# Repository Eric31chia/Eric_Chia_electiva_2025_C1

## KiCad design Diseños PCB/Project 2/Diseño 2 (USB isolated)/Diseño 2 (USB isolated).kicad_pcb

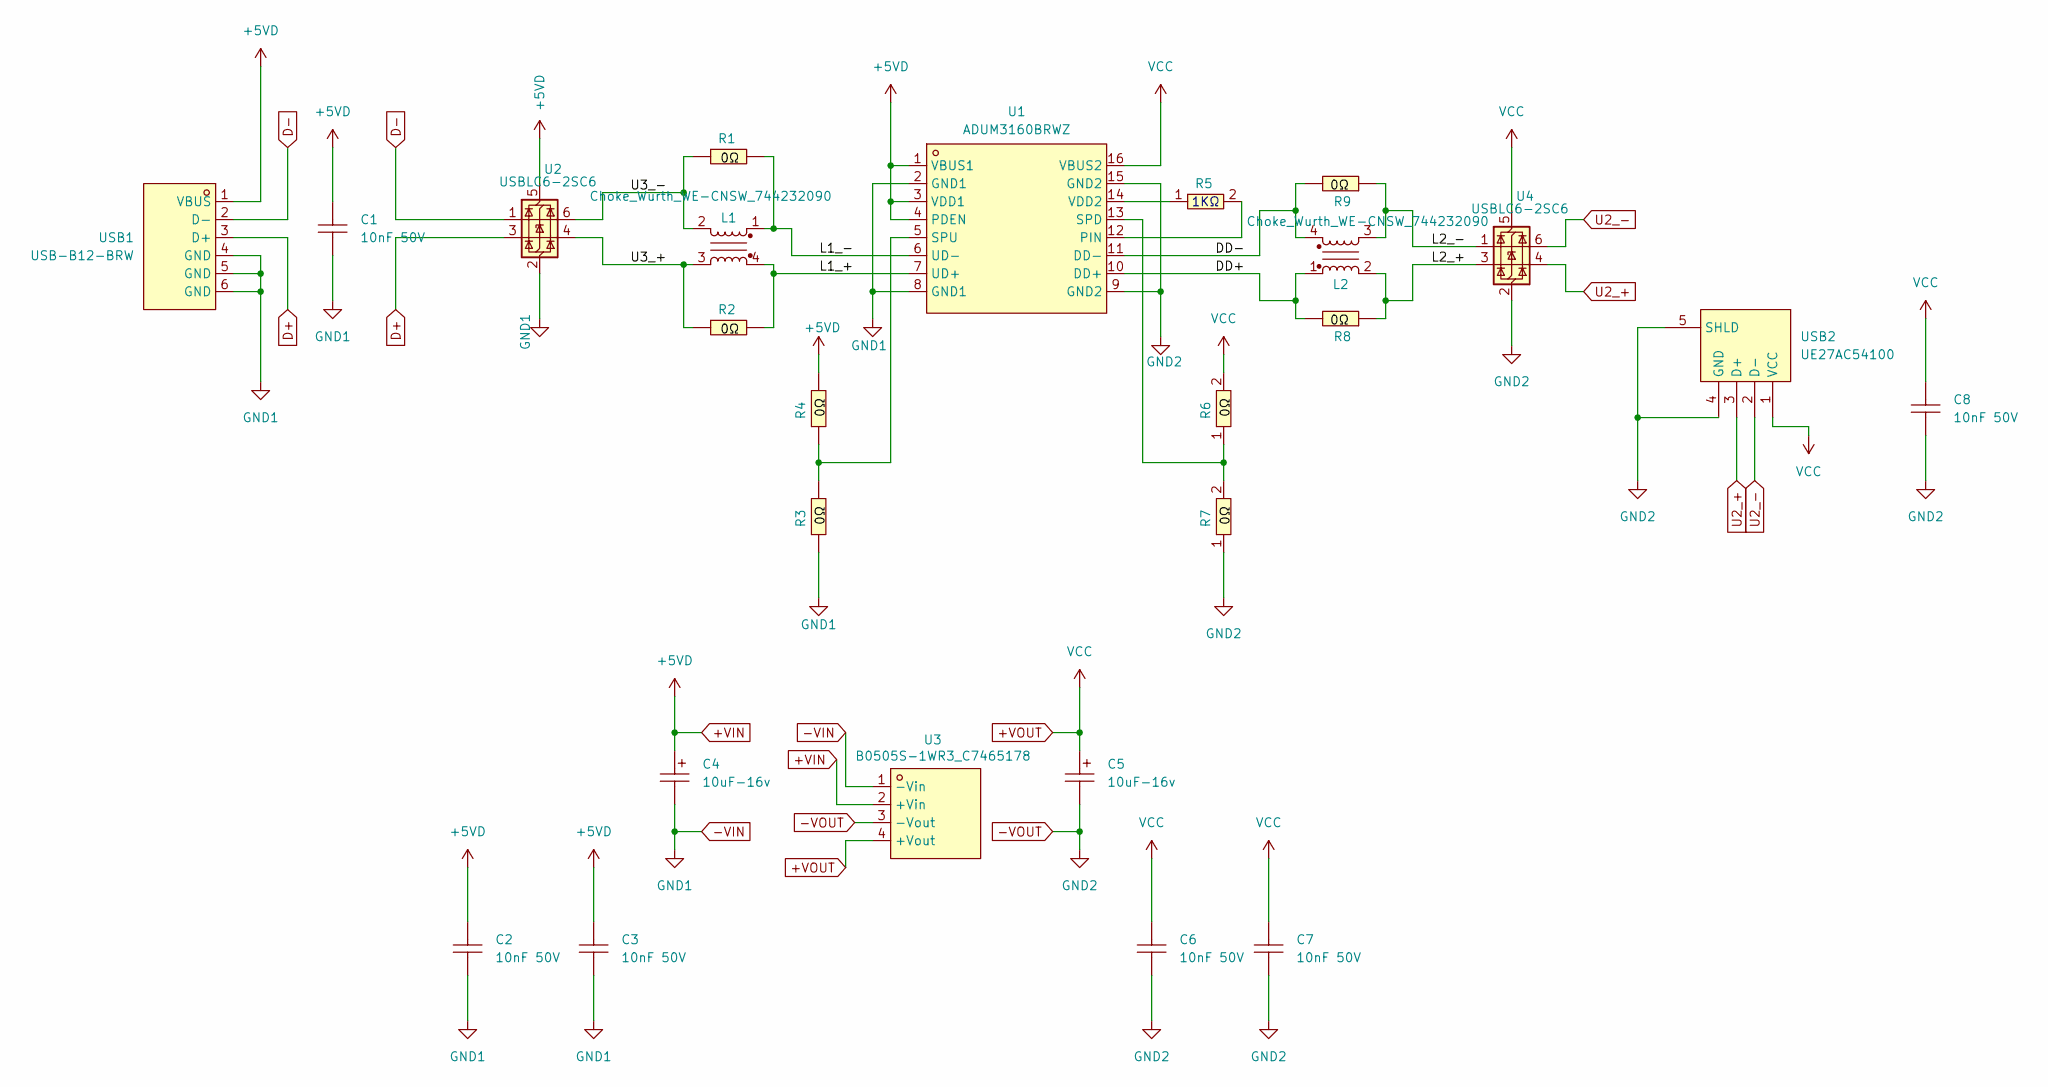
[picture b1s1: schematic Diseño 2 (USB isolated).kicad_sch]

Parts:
C1, C2, C3, C6, C7, C8: 10nF 50V; C0402; LCSC Part C60133
C4, C5: 10uF-16v; CAP-SMD_L3.2-W1.6-RD; LCSC Part C128254
L1, L2: Choke_Wurth_WE-CNSW_744232090; L_CommonMode_Wurth_WE-CNSW-1206
R1, R2, R3, R4, R5, R6, R7, R8, R9: RC0402FR-070RL; R0402; LCSC Part C106231
U1: ADUM3160BRWZ; WSOIC-16_L10.3-W7.5-P1.27-LS10.3-BL; LCSC Part C108501
U2, U4: USBLC6-2SC6; SOT-23-6
U3: B0505S-1WR3_C7465178; PWRM-TH_B0505S-1WR3; LCSC Part C7465178
USB1: USB-B12-BRW; USB-B-TH_USB-B12-BRW; LCSC Part C720550
USB2: UE27AC54100; USB-A-TH_UE27AC54100; LCSC Part C464564

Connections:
+VIN: C1.1, C2.1, C3.1, C4.1, R4.2, U1.1 (VBUS1), U1.3 (VDD1), U1.4 (PDEN), U2.5 (VBUS), U3.2 (+Vin), USB1.1 (VBUS)
+VOUT: C5.1, C6.1, C7.1, C8.1, R6.2, U1.16 (VBUS2), U3.4 (+Vout), U4.5 (VBUS), USB2.1 (VCC)
-VIN: C1.2, C2.2, C3.2, C4.2, R3.1, U1.2 (GND1), U1.8 (GND1), U2.2 (GND), U3.1 (-Vin), USB1.4 (GND), USB1.5 (GND), USB1.6 (GND)
-VOUT: C5.2, C6.2, C7.2, C8.2, R7.1, U1.9 (GND2), U1.15 (GND2), U3.3 (-Vout), U4.2 (GND), USB2.4 (GND), USB2.5 (SHLD)
/DD+: L2.1, R8.2, U1.10 (DD+)
/DD-: L2.4, R9.2, U1.11 (DD-)
/L1_+: L1.4, R2.2, U1.7 (UD+)
/L1_-: L1.1, R1.2, U1.6 (UD-)
/L2_+: L2.2, R8.1, U4.3 (I/O2)
/L2_-: L2.3, R9.1, U4.1 (I/O1)
/U3_+: L1.3, R2.1, U2.4 (I/O2)
/U3_-: L1.2, R1.1, U2.6 (I/O1)
D+: U2.3 (I/O2), USB1.3 (D+)
D-: U2.1 (I/O1), USB1.2 (D-)
unnamed: R5.2, U1.12 (PIN)
unnamed: R6.1, R7.2, U1.13 (SPD)
unnamed: R3.2, R4.1, U1.5 (SPU)
unnamed: R5.1, U1.14 (VDD2)
U2_+: U4.4 (I/O2), USB2.3 (D+)
U2_-: U4.6 (I/O1), USB2.2 (D-)

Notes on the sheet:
1KΩ

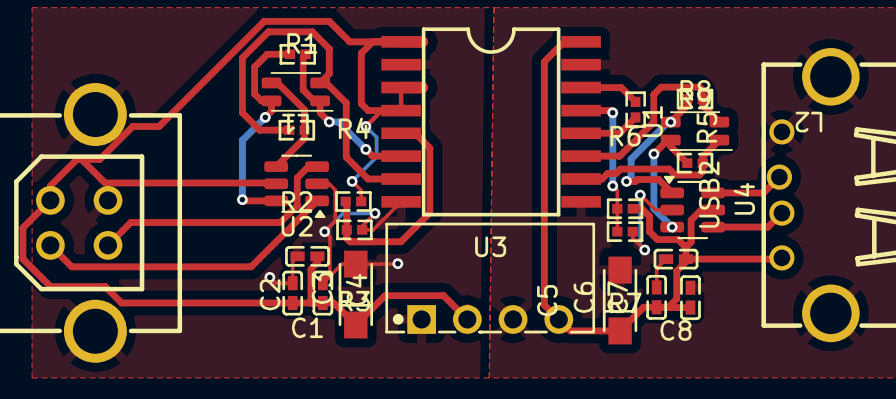
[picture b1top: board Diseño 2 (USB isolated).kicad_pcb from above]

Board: 2 copper layers, 25 parts (0 on the bottom side), 20 nets.

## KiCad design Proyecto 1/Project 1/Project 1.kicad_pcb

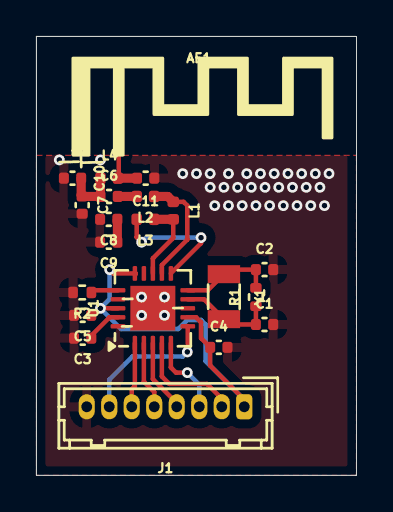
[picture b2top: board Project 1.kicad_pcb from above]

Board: 2 copper layers, 17.8 x 24.4 mm, 21 parts (0 on the bottom side), 18 nets.

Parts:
AE1: Antenna; Texas_SWRA117D_2.4GHz_Right
C1, C2: 22p; C_0402_1005Metric
C3, C4, C5: C_Small; C_0402_1005Metric
C6: 1p5; C_0402_1005Metric
C7: 1p; C_0402_1005Metric
C8: 10n; C_0402_1005Metric
C9: 1n; C_0402_1005Metric
C10, C11: Cx; C_0402_1005Metric
J1: Conn_01x08_Pin; Hirose_DF13-08P-1.25DSA_1x08_P1.25mm_Vertical
L1: 8n2; L_0402_1005Metric
L2: 3n9; L_0402_1005Metric
L3: 2n7; L_0402_1005Metric
L4: Lx; L_0402_1005Metric
R1: 10M; R_0402_1005Metric
R2: 22k; R_0402_1005Metric
U1: NRF24L01; QFN-20-1EP_4x4mm_P0.5mm_EP2.5x2.5mm
Y1: 16MHz; Crystal_SMD_3215-2Pin_3.2x1.5mm

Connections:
GND: C1.2, C2.2, C3.2, C4.2, C5.2, C7.2, C8.2, C9.2, C10.2, C11.2, J1.8, R2.2, U1.8 (VSS), U1.14 (VSS), U1.17 (VSS), U1.20 (VSS)
unnamed: AE1.1 (A), C11.1, L4.2
unnamed: C6.2, L2.2
unnamed: C6.1, C7.1, C10.1, L4.1
unnamed: J1.2, U1.4 (MOSI)
unnamed: J1.3, U1.5 (MISO)
unnamed: J1.4, U1.3 (SCK)
unnamed: J1.5, U1.2 (CSN)
unnamed: J1.6, U1.1 (CE)
unnamed: J1.7, U1.6 (IRQ)
unnamed: L1.1, L2.1, U1.12 (ANT1)
unnamed: L1.2, L3.1, U1.13 (ANT2)
unnamed: C3.1, U1.19 (DVDD)
unnamed: R2.1, U1.16 (IREF)
unnamed: L3.2, U1.11 (VDD_PA)
unnamed: C2.1, R1.1, U1.10 (XC1), Y1.2
unnamed: C1.1, R1.2, U1.9 (XC2), Y1.1
VDD: C4.1, C5.1, C8.1, C9.1, J1.1, U1.7 (VDD), U1.15 (VDD), U1.18 (VDD)

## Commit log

2025-01-21 eric chia
2025-01-21 eliminado ya que era prueba
2025-01-24 Tarea 1 diseño
2025-01-31 Resumen comandos basicos de GIT
2025-03-22 resumen
2025-03-28 Producto norma IEEE-830
2025-04-25 Disenos de la cara y base del pcb
2025-04-26 parte trasera
2025-06-05 vaina rara
